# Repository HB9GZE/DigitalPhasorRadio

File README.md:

Use these SW version of the development tools:
Cube MX: 6.13.0
Cube IDE: 1.17.0
Touch GFX Generator: 4.23.0
STM32H735: 1.12.0
FreeRTOS: 1.2.0

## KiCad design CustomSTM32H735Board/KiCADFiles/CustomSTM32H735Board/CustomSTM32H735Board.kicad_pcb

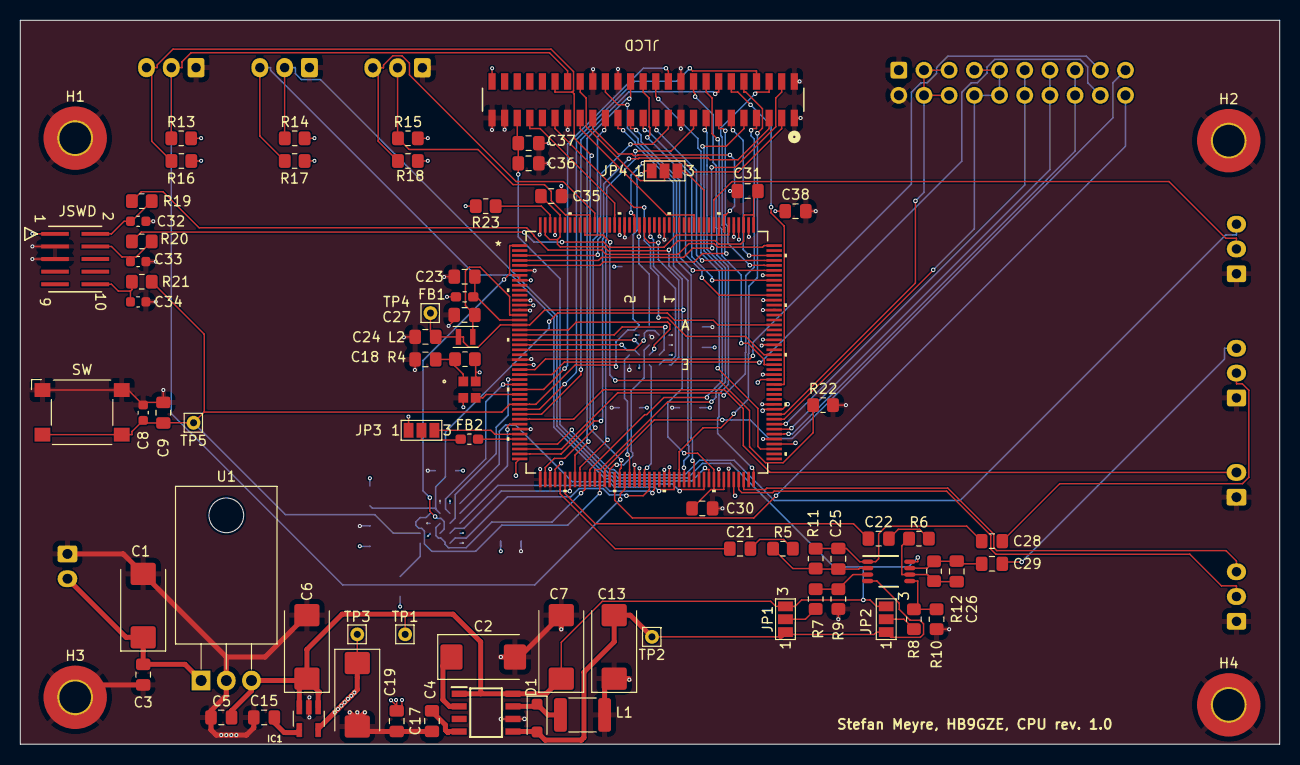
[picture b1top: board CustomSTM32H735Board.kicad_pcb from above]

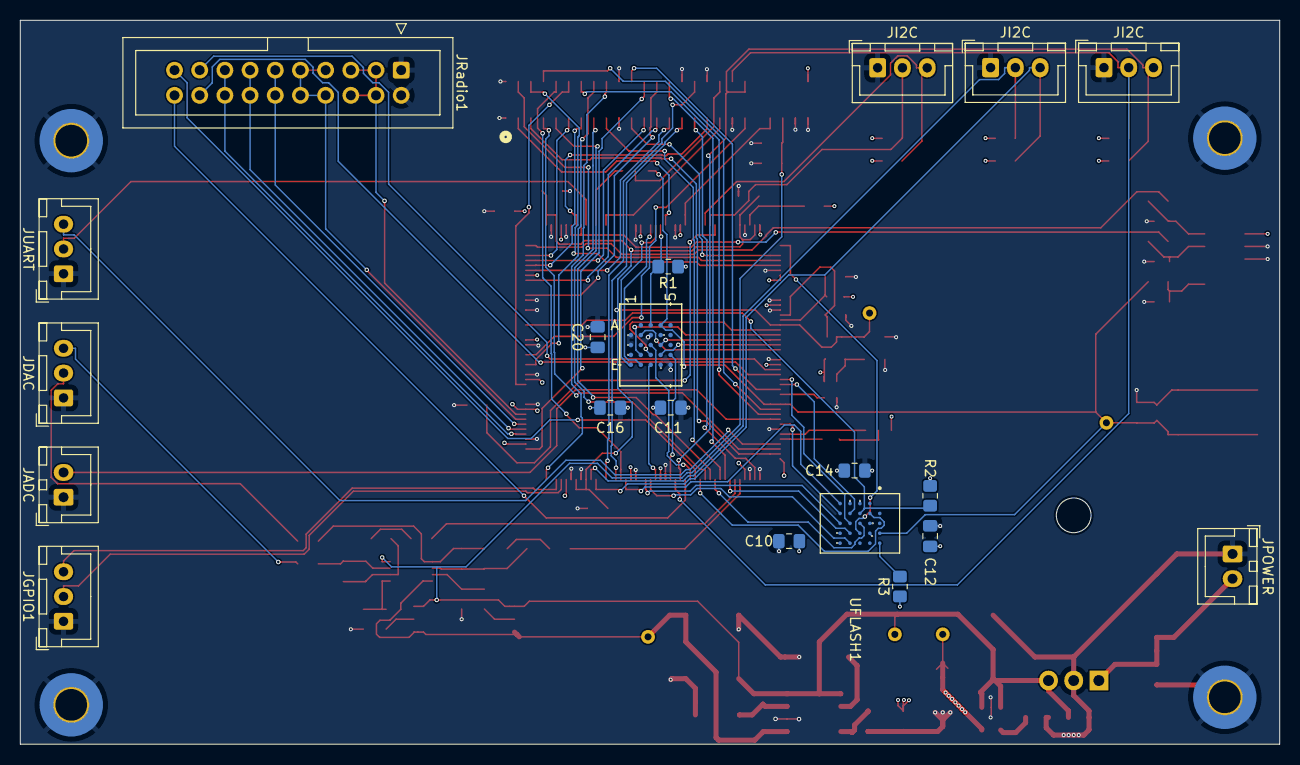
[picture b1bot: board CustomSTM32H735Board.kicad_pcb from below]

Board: 4 copper layers, 127.0 x 73.0 mm, 99 parts (20 on the bottom side), 115 nets.

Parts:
C1, C6: 47uF Tant. 25V; CP_EIA-7343-30_AVX-N_Pad2.25x2.55mm_HandSolder
C2, C19: 10uF Tant. 25V; CP_EIA-7343-30_AVX-N_Pad2.25x2.55mm_HandSolder
C3, C5, C9, C10, C11, C12, C14, C16, C17, C18, C20, C37, C38: 100nF; C_0805_2012Metric_Pad1.18x1.45mm_HandSolder
C4: optional: 82pF; C_0805_2012Metric_Pad1.18x1.45mm_HandSolder
C7: 1uF, Tant. 25V; CP_EIA-7343-30_AVX-N_Pad2.25x2.55mm_HandSolder
C8, C32, C33, C34: PGB1010603; C_0603_1608Metric
C13: 100uF Tant. 25V; CP_EIA-7343-30_AVX-N_Pad2.25x2.55mm_HandSolder
C15: 1uF; C_0805_2012Metric_Pad1.18x1.45mm_HandSolder
C21, C22, C23, C24, C28, C29, C36: 10uF; C_0805_2012Metric_Pad1.18x1.45mm_HandSolder
C25, C26: 1nF; C_0805_2012Metric_Pad1.18x1.45mm_HandSolder
C27: 220pF; C_0805_2012Metric_Pad1.18x1.45mm_HandSolder
C30, C31, C35: 4.7uF low ESR; C_0805_2012Metric_Pad1.18x1.45mm_HandSolder
D1: PMEG2010AEH; D_SOD-123F
FB1: FBMJ1608; L_0603_1608Metric_Pad1.05x0.95mm_HandSolder
FB2: FCM1608; L_0603_1608Metric_Pad1.05x0.95mm_HandSolder
H1, H2, H3, H4: MountingHole_Pad; MountingHole_3.2mm_M3_Pad_TopBottom
IC1: NCP700BSN33T1G; SOT95P275X120-5N
JADC: Conn_01x02_Socket; JST_XH_B2B-XH-A_1x02_P2.50mm_Vertical
JDAC: Conn_01x03_Socket; JST_XH_B3B-XH-A_1x03_P2.50mm_Vertical
JGPIO1: Conn_01x03_Socket; JST_XH_B3B-XH-A_1x03_P2.50mm_Vertical
JI2C, JI2C#2, JI2C#3: Conn_01x03_Socket; JST_XH_B3B-XH-A_1x03_P2.50mm_Vertical
JLCD: FLE-125-01-G-DV; CON50_2X25_UF_FLE_SAI
JP1, JP2, JP3, JP4: SolderJumper_3_Open; SolderJumper-3_P1.3mm_Open_Pad1.0x1.5mm_NumberLabels
JPOWER: Conn_01x02_Socket; JST_XH_B2B-XH-A_1x02_P2.50mm_Vertical
JRadio1: Conn_02x10_Odd_Even; IDC-Header_2x10_P2.54mm_Vertical
JSWD: FTSH-105-01-L-DV-K; CON10_2X5_DUK_FTSH_SAI-M
JUART: Conn_01x03_Socket; JST_XH_B3B-XH-A_1x03_P2.50mm_Vertical
L1: 10uH; L_1812_4532Metric_Pad1.30x3.40mm_HandSolder
L2: 2.2uH; L_Murata_DFE201610P
PS1: TPS6735ID; SOIC127P600X175-8N
R1, R2, R3, R4, R5, R6, R7, R8, R9, R10, R11, R12: 10k; R_0805_2012Metric_Pad1.20x1.40mm_HandSolder
R13, R14, R15, R16, R17, R18: 4.7k; R_0805_2012Metric_Pad1.20x1.40mm_HandSolder
R19, R20, R21: 22R; R_0805_2012Metric_Pad1.20x1.40mm_HandSolder
R22: 5k1; R_0805_2012Metric_Pad1.20x1.40mm_HandSolder
R23: 1k; R_0805_2012Metric_Pad1.20x1.40mm_HandSolder
SW: SW_Omron_B3FS; SW_SPST_Omron_B3FS-100xP
TP1, TP2, TP3, TP4, TP5: TestPoint; Pin_D0.7mm_L6.5mm_W1.8mm_FlatFork
U1: L7805; TO-220-3_Horizontal_TabDown
U2: OPA1678IDGKT; OPA1678_L
U3: STM32H735IGT6; LQFP176_STM32H735IGT6_STM-M
UFLASH1: MX25LM51245GXDI00; BGA24C100P5X5_600X800X120
UHYPERRAM1: IS66WVH16M8DBLL-100B1LI; TFBGA24_6X8_ISI
X1: NSC5004A-25M; NSC5004_NDK

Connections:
+3.3V: C10.1, C11.1, C12.1, C14.1, C16.1, C17.1, C19.1, C20.1, C38.1, FB1.1, IC1.5 (OUT), JLCD.50, JP3.1 (A), JSWD.1, R1.1, R2.1, R3.1, R4.1, R13.2, R14.2, R15.2, R16.2, R17.2, R18.2, R23.2, TP3.1, U3.7, U3.8, U3.13, U3.25, U3.44, U3.48, U3.65, U3.71, U3.84, U3.92, U3.99, U3.105, U3.113, U3.126, U3.136, U3.152, U3.160, U3.176, UFLASH1.B4 (VCC), UFLASH1.D1 (VCCQ), UFLASH1.E4 (VCCQ__1), UHYPERRAM1.B4 (VCC), UHYPERRAM1.D1 (VCCQ), UHYPERRAM1.E4 (VCCQ), X1.4 (VCC)
+5V: C5.1, C6.1, C7.1, C36.1, C37.1, IC1.1 (IN), IC1.3 (EN), JLCD.45, JP1.3 (B), JP2.3 (B), PS1.1 (EN), PS1.8 (VCC), TP1.1, U1.3 (OUT), U2.8 (V+)
-5V: C13.2, D1.2 (A), JP1.1 (A), JP2.1 (A), PS1.5 (FB), TP2.1, U2.4 (V-)
/BOOT0: R22.1, U3.167
/NRST: C8.2, C9.1, JP4.1 (A), R21.1, SW.2, TP5.1, U3.33, UFLASH1.A4 (~RESET), UHYPERRAM1.A4 (RESET#)
/PA0: JUART.3, U3.41 (PA0-UART4_TX)
/PA1: JLCD.7, U3.42 (PA1-LTDC_R2)
/PA2: JLCD.5, U3.43 (PA2-LTDC_R1)
/PA3: JLCD.31, U3.46 (PA3-LTDC_B5)
/PA4: C21.1, U3.49 (PA4-DAC1_OUT1)
/PA5: C22.1, U3.50 (PA5-DAC1_OUT2)
/PA6: U3.51 (PA6-OCTOSPIM_P1_IO3), UFLASH1.D4 (SIO3)
/PA7: JLCD.28, U3.52 (PA7-LTDC_VSYNC)
/PA8: JLCD.27, U3.127 (PA8-LTDC_B3)
/PA9: JLCD.13, U3.128 (PA9-LTDC_R5)
/PA10: JLCD.23, U3.129 (PA10-LTDC_B1)
/PA11: JLCD.11, U3.130 (PA11-LTDC_R4)
/PA13: R19.1, U3.132 (PA13(JTMS/SWDIO)-DEBUG_JTMS-SWDIO)
/PA14: R20.1, U3.138 (PA14(JTCK/SWCLK)-DEBUG_JTCK-SWCLK), U3.140
/PA15: JLCD.33, U3.139 (PA15(JTDI)-LTDC_B6)
/PB0: JLCD.9, U3.55 (PB0-LTDC_R3)
/PB1: JLCD.15, U3.56 (PB1-LTDC_R6)
/PB2: U3.57 (PB2-OCTOSPIM_P1_CLK), UFLASH1.B2 (SCLK)
/PB6: JI2C.3, R18.1, U3.165 (PB6-I2C1_SCL)
/PB7: JI2C.2, R15.1, U3.166 (PB7-I2C1_SDA)
/PB10: JI2C#3.3, R17.1, U3.78 (PB10-I2C2_SCL)
/PB11: JI2C#3.2, R14.1, U3.79 (PB11-I2C2_SDA)
/PB12: JGPIO1.2, U3.85 (PB12-GPIO_Output)
/PB13: JGPIO1.3, U3.86 (PB13-GPIO_Output)
/PB15: JLCD.18, U3.88 (PB15-LTDC_G7)
/PC0: JLCD.8, U3.34 (PC0-LTDC_G2)
/PC1: JLCD.14, U3.35 (PC1-LTDC_G5)
/PC2_C: JADC.2, U3.36 (PC2_C-ADC3_INP0)
/PC3_C: U3.37 (PC3_C-OCTOSPIM_P1_IO6), UFLASH1.E2 (SIO6)
/PC4: JLCD.17, U3.53 (PC4-LTDC_R7)
/PC5: U3.54 (PC5-OCTOSPIM_P1_DQS), UFLASH1.C3 (DQS)
/PC6: JLCD.26, U3.122 (PC6-LTDC_HSYNC)
/PC9: JLCD.25, U3.125 (PC9-LTDC_B2)
/PC11: JUART.2, U3.141 (PC11-UART4_RX)
/PD0: JP4.3 (B), U3.143
/PD2: JLCD.35, U3.145 (PD2-LTDC_B7)
/PD10: JLCD.24, U3.91 (PD10-GPIO_Output)
/PD11: JRadio1.15, JRadio1.16, U3.94 (PD11-GPIO_Output)
/PD12: JRadio1.13, JRadio1.14, U3.95 (PD12-GPIO_Output)
/PD13: JRadio1.11, JRadio1.12, U3.96 (PD13-GPIO_Output)
/PD14: JRadio1.7, JRadio1.8, JRadio1.9, JRadio1.10, U3.97 (PD14-GPIO_Output)
/PD15: JRadio1.3, JRadio1.4, JRadio1.5, JRadio1.6, U3.98 (PD15-GPIO_Output)
/PDR_ON: R23.1, U3.174
/PE2: U3.1 (PE2-OCTOSPIM_P1_IO2), UFLASH1.C4 (SIO2)
/PE4: JLCD.21, U3.3 (PE4-LTDC_B0)
/PE5: JLCD.4, U3.4 (PE5-LTDC_G0)
/PE6: JLCD.6, U3.5 (PE6-LTDC_G1)
/PE7: U3.67 (PE7-OCTOSPIM_P1_IO4), UFLASH1.D5 (SIO4)
/PE8: U3.68 (PE8-OCTOSPIM_P1_IO5), UFLASH1.E3 (SIO5)
/PE10: U3.72 (PE10-OCTOSPIM_P1_IO7), UFLASH1.E1 (SIO7)
/PE11: JLCD.10, U3.73 (PE11-LTDC_G3)
/PE12: JLCD.29, U3.74 (PE12-LTDC_B4)
/PE14: JLCD.32, U3.76 (PE14-LTDC_CLK)
/PF0: U3.18 (PF0-OCTOSPIM_P2_IO0), UHYPERRAM1.D3 (DQ0)
/PF1: U3.19 (PF1-OCTOSPIM_P2_IO1), UHYPERRAM1.D2 (DQ1)
/PF2: U3.20 (PF2-OCTOSPIM_P2_IO2), UHYPERRAM1.C4 (DQ2)
/PF3: U3.21 (PF3-OCTOSPIM_P2_IO3), UHYPERRAM1.D4 (DQ3)
/PF4: U3.22 (PF4-OCTOSPIM_P2_CLK), UHYPERRAM1.B2 (CK)
/PF6: JRadio1.17, U3.26 (PF6-TIM23_CH1)
/PF7: JRadio1.18, U3.27 (PF7-TIM23_CH2)
/PF8: U3.28 (PF8-OCTOSPIM_P1_IO0), UFLASH1.D3 (SI/SIO0)
/PF9: U3.29 (PF9-OCTOSPIM_P1_IO1), UFLASH1.D2 (SO/SIO1)
/PF10: JLCD.22, U3.30 (PF10-LTDC_DE)
/PF11: JRadio1.19, U3.58 (PF11-ADC1_INP2)
/PF12: U3.59 (PF12-OCTOSPIM_P2_DQS), UHYPERRAM1.C3 (RWDS)
/PF13: JRadio1.20, U3.60 (PF13-ADC2_INP2)
/PF14: JI2C#2.3, JLCD.40, R16.1, U3.61 (PF14-I2C4_SCL)
/PF15: JI2C#2.2, JLCD.38, R13.1, U3.62 (PF15-I2C4_SDA)
/PG0: U3.63 (PG0-OCTOSPIM_P2_IO4), UHYPERRAM1.D5 (DQ4)
/PG1: U3.66 (PG1-OCTOSPIM_P2_IO5), UHYPERRAM1.E3 (DQ5)
/PG2: JLCD.39, U3.110 (PG2-GPIO_EXTI2)
/PG6: R2.2, U3.116 (PG6-OCTOSPIM_P1_NCS), UFLASH1.C2 (~CS)
/PG10: U3.154 (PG10-OCTOSPIM_P2_IO6), UHYPERRAM1.E2 (DQ6)
/PG11: U3.155 (PG11-OCTOSPIM_P2_IO7), UHYPERRAM1.E1 (DQ7)
/PG12: R1.2, U3.156 (PG12-OCTOSPIM_P2_NCS), UHYPERRAM1.A3 (CS#)
/PG13: JLCD.3, U3.157 (PG13-LTDC_R0)
/PG15: JLCD.43, U3.161 (PG15-GPIO_Output)
/PH0: U3.31 (PH0-OSC_IN-RCC_OSC_IN), X1.3 (OUTPUT)
/PJ11: JLCD.12, U3.104 (PJ11-LTDC_G4)
/PK1: JLCD.16, U3.108 (PK1-LTDC_G6)
/VDDSMPS: C23.1, FB1.2, U3.16
/VDD_SDC: C24.1, C30.2, C31.1, C35.2, L2.1, TP4.1, U3.17, U3.80, U3.82, U3.133, U3.135, U3.172, U3.175
/VLXSMPS: C27.2, L2.2, U3.15
GND: C1.2, C2.2, C3.2, C4.2, C5.2, C6.2, C7.2, C8.1, C9.2, C10.2, C11.2, C12.2, C13.1, C14.2, C15.1, C16.2, C17.2, C18.1, C19.2, C20.2, C23.2, C24.2, C27.1, C30.1, C31.2, C32.2, C33.1, C34.1, C35.1, C36.2, C37.2, C38.2, H1.1, H2.1, H3.1, H4.1, IC1.2 (GND), JADC.1, JDAC.1, JGPIO1.1, JI2C.1, JI2C#2.1, JI2C#3.1, JLCD.1, JLCD.2, JLCD.19, JLCD.20, JLCD.30, JLCD.34, JLCD.37, JLCD.47, JLCD.49, JPOWER.1, JRadio1.1, JRadio1.2, JSWD.3, JSWD.5, JUART.1, L1.2, PS1.6 (GND), R9.1, R10.1, R22.2, SW.1, U1.2 (GND), U3.6, U3.12, U3.14, U3.24, U3.38, U3.45, U3.47, U3.64, U3.70, U3.81, U3.83, U3.93, U3.100, U3.106, U3.112, U3.119, U3.121, U3.134, U3.137, U3.151, U3.159, U3.173, UFLASH1.B3 (GND), UFLASH1.C1 (VSSQ), UFLASH1.E5 (VSSQ__1), UHYPERRAM1.B1 (CK#), UHYPERRAM1.B3 (VSS), UHYPERRAM1.C1 (VSSQ), UHYPERRAM1.E5 (VSSQ), X1.2 (GND)
unnamed: C21.2, R5.2
unnamed: C22.2, R6.2
unnamed: C32.1, JSWD.2, R19.2
unnamed: C33.2, JSWD.4, R20.2
unnamed: C34.2, JSWD.10, R21.2
unnamed: D1.1 (K), L1.1, PS1.7 (OUT)
unnamed: FB2.2, U3.40
unnamed: C15.2, IC1.4 (BYP)
unnamed: C28.2, JDAC.2
unnamed: C29.2, JDAC.3
unnamed: JP1.2 (C), R7.2
unnamed: JP2.2 (C), R8.2
unnamed: JP3.3 (B), U3.39
unnamed: FB2.1, JP3.2 (C)
unnamed: JLCD.36, JP4.2 (C)
unnamed: C1.1, C3.1, JPOWER.2, U1.1 (IN)
unnamed: C4.1, PS1.4 (COMP)
unnamed: C2.1, PS1.2 (REF)
unnamed: R7.1, R9.2, U2.3 (IN+)
unnamed: C25.1, R5.1, R11.2, U2.2 (IN-)
unnamed: C25.2, C28.1, R11.1, U2.1 (OUT)
unnamed: R8.1, R10.2, U2.5 (IN+)
unnamed: C26.1, R6.1, R12.2, U2.6 (IN-)
unnamed: C26.2, C29.1, R12.1, U2.7 (OUT)
unnamed: R3.2, UFLASH1.A5 (~ECS)
unnamed: C18.2, R4.2, X1.1 (STAND-BY)

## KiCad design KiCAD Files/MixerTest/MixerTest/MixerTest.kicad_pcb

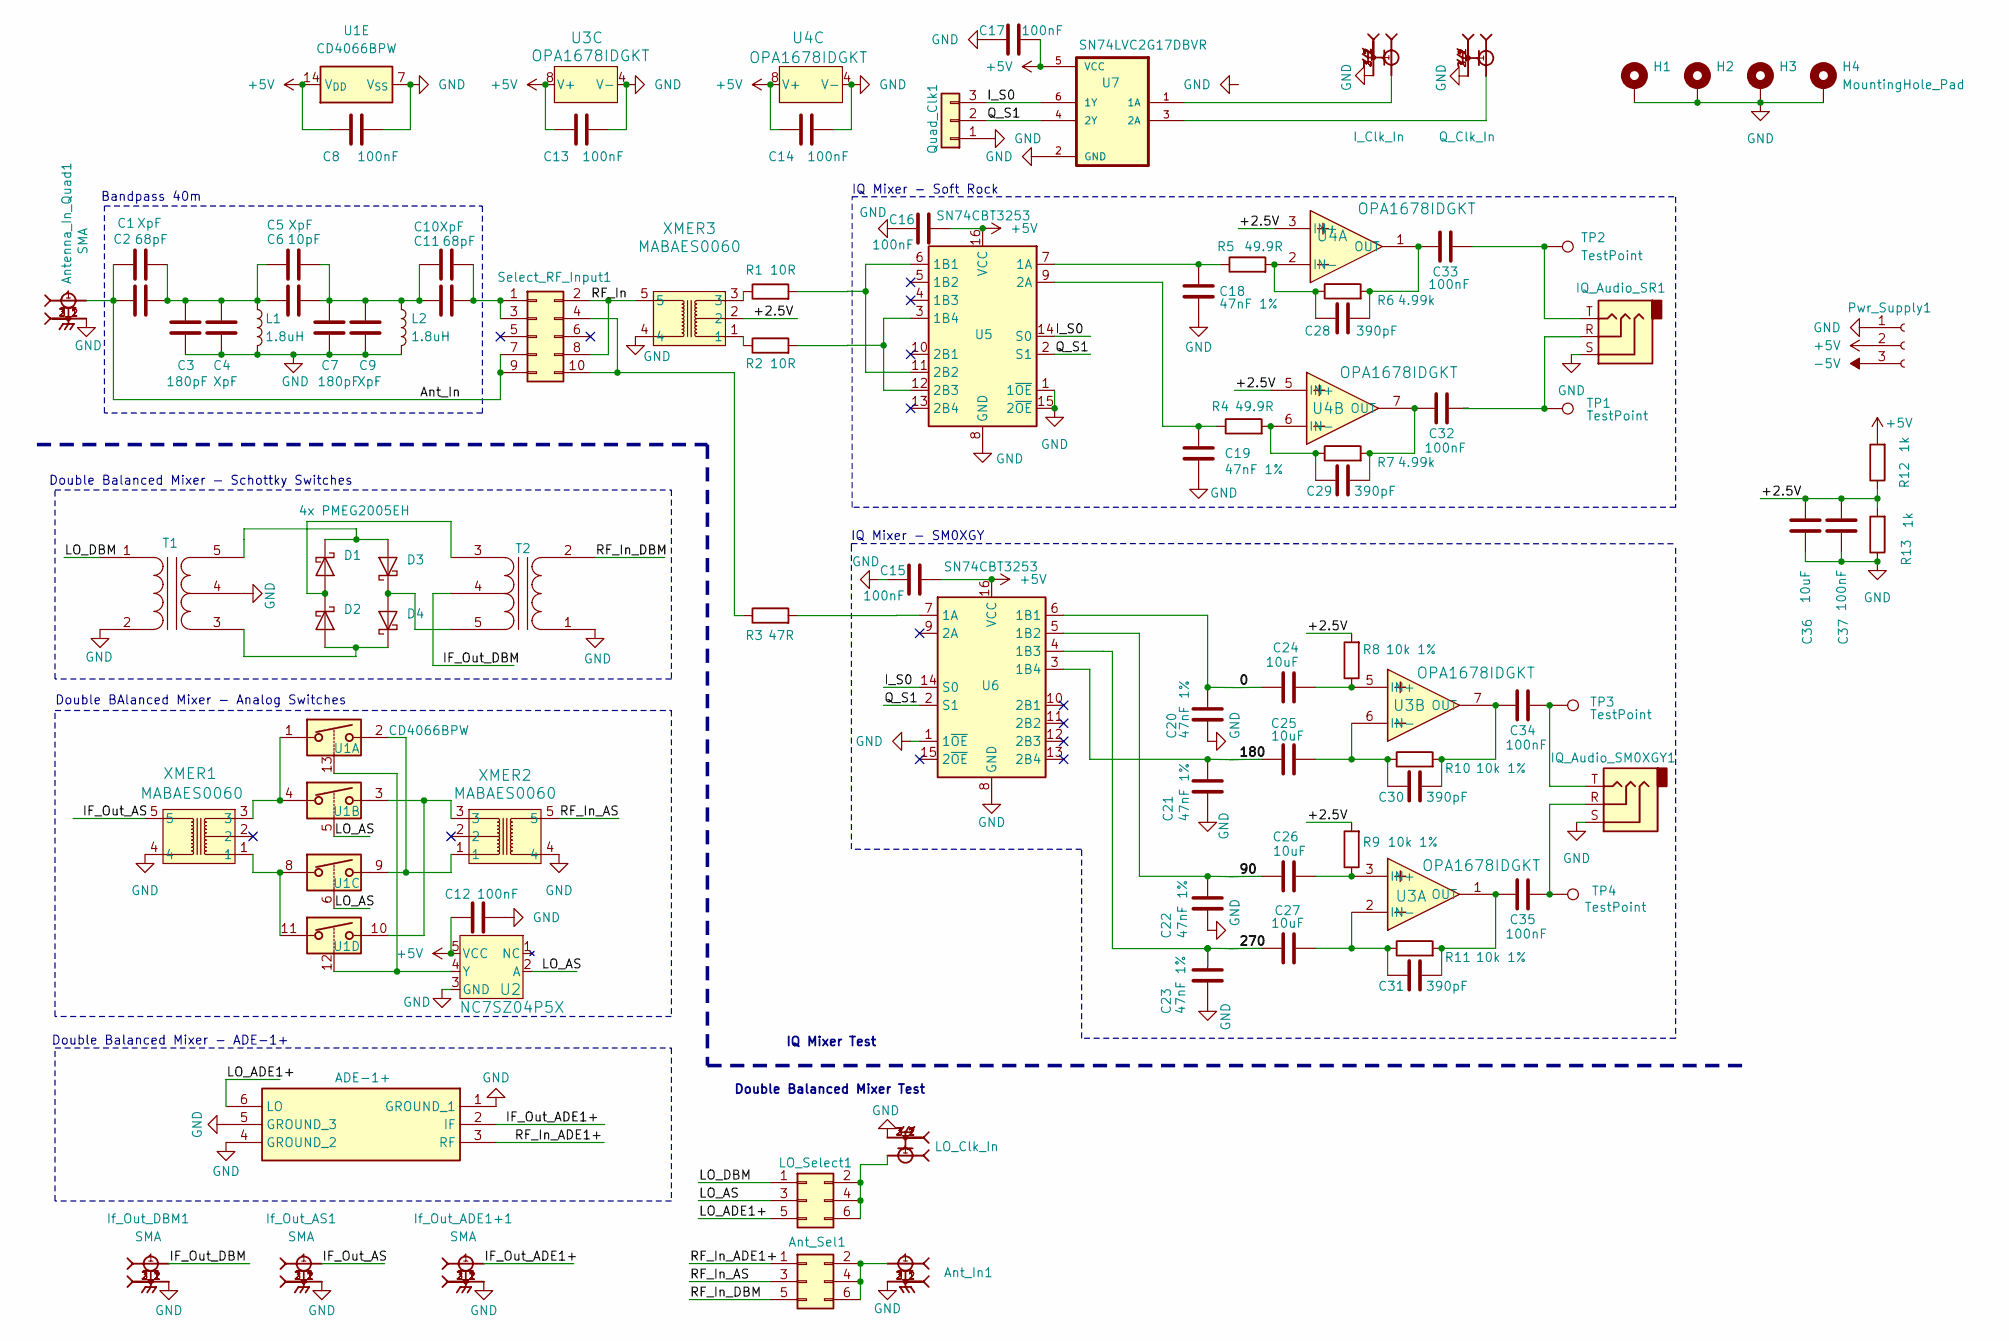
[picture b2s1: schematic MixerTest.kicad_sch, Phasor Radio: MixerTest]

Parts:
Ant_In1: SMA; SAMTEC_SMA-J-P-H-ST-EM1
Ant_Sel1: Conn_02x03_Odd_Even; PinHeader_2x03_P2.54mm_Vertical
Antenna_In_Quad1: SMA; SAMTEC_SMA-J-P-H-ST-EM1
C1, C4, C5, C9, C10: XpF; C_0805_2012Metric_Pad1.18x1.45mm_HandSolder
C2, C11: 68pF; C_0805_2012Metric_Pad1.18x1.45mm_HandSolder
C3, C7: 180pF; C_0805_2012Metric_Pad1.18x1.45mm_HandSolder
C6: 10pF; C_0805_2012Metric_Pad1.18x1.45mm_HandSolder
C8, C12, C13, C14, C15, C16, C17, C32, C33, C34, C35, C37: 100nF; C_0805_2012Metric_Pad1.18x1.45mm_HandSolder
C18, C19, C20, C21, C22, C23: 47nF 1%; C_0805_2012Metric_Pad1.18x1.45mm_HandSolder
C24, C25, C26, C27, C36: 10uF; C_0805_2012Metric_Pad1.18x1.45mm_HandSolder
C28, C29, C30, C31: 390pF; C_0805_2012Metric_Pad1.18x1.45mm_HandSolder
D1: 4x PMEG2005EH; D_SOD-123F
D2, D3, D4: PMEG2005EH; D_SOD-123F
H1, H2, H3, H4: MountingHole_Pad; MountingHole_2.5mm_Pad_TopBottom
IC1: ADE-1+; ADE1Mix; Manufacturer_Part_Number ADE-1+; Mouser Part Number 139-ADE-1
IQ_Audio_SM0XGY1: AudioJack3; Jack_3.5mm_CUI_SJ-3523-SMT_Horizontal
IQ_Audio_SR1: AudioJack3; Jack_3.5mm_CUI_SJ-3523-SMT_Horizontal
I_Clk_In: SMA; SAMTEC_SMA-J-P-H-ST-EM1
If_Out_ADE1+1: SMA; SAMTEC_SMA-J-P-H-ST-EM1
If_Out_AS1: SMA; SAMTEC_SMA-J-P-H-ST-EM1
If_Out_DBM1: SMA; SAMTEC_SMA-J-P-H-ST-EM1
L1, L2: 1.8uH; L_Toroid_Vertical_L19.1mm_W8.1mm_P7.10mm_Bourns_5700
LO_Clk_In: SMA; SAMTEC_SMA-J-P-H-ST-EM1
LO_Select1: Conn_02x03_Odd_Even; PinSocket_2x03_P2.54mm_Vertical
Pwr_Supply1: Conn_01x03_Socket; JST_EH_B3B-EH-A_1x03_P2.50mm_Vertical
Q_Clk_In: SMA; SAMTEC_SMA-J-P-H-ST-EM1
Quad_Clk1: Conn_01x03; PinHeader_1x03_P2.54mm_Vertical
R1, R2: 10R; R_0805_2012Metric_Pad1.20x1.40mm_HandSolder
R3: 47R; R_0805_2012Metric_Pad1.20x1.40mm_HandSolder
R4, R5: 49.9R; R_0805_2012Metric_Pad1.20x1.40mm_HandSolder
R6, R7: 4.99k; R_0805_2012Metric_Pad1.20x1.40mm_HandSolder
R8, R9, R10, R11: 10k 1%; R_0805_2012Metric_Pad1.20x1.40mm_HandSolder
R12, R13: 1k; R_0805_2012Metric_Pad1.20x1.40mm_HandSolder
Select_RF_Input1: Conn_02x05_Odd_Even; PinHeader_2x05_P2.54mm_Vertical
T1, T2: Transformer_1P_SS_SNM
TP1, TP2, TP3, TP4: TestPoint; TestPoint_Loop_D1.80mm_Drill1.0mm_Beaded
U1: CD4066BPW; TSSOP-14_4.4x5mm_P0.65mm
U2: NC7SZ04P5X; SC-88A-5_1P35X2P2_ONS
U3, U4: OPA1678IDGKT; OPA1678_L
U5, U6: SN74CBT3253; SOP65P640X110-16N
U7: SN74LVC2G17DBVR; SOT95P280X145-6N
XMER1, XMER2, XMER3: MABAES0060; MABAES0060_MCM

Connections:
+5V: C8.1, C12.2, C13.1, C14.1, C15.2, C16.2, C17.2, Pwr_Supply1.2, R12.2, U1.14 (V_{DD}), U2.5 (VCC), U3.8 (V+), U4.8 (V+), U5.16 (VCC), U6.16 (VCC), U7.5 (VCC)
-5V: Pwr_Supply1.3
/0: C20.1, C24.1, U6.6 (1B1)
/90: C22.1, C26.1, U6.5 (1B2)
/180: C21.1, C25.1, U6.3 (1B4)
/270: C23.1, C27.1, U6.4 (1B3)
/Ant_In: Antenna_In_Quad1.1, C1.1, C2.1, Select_RF_Input1.7, Select_RF_Input1.9
/IF_Out_ADE1+: IC1.2 (IF), If_Out_ADE1+1.1
/IF_Out_AS: If_Out_AS1.1, XMER1.5
/IF_Out_DBM: If_Out_DBM1.1, T2.4 (SC)
/I_S0: Quad_Clk1.3, U5.14 (S0), U6.14 (S0), U7.6 (1Y)
/LO_ADE1+: IC1.6 (LO), LO_Select1.5
/LO_AS: LO_Select1.3, U1.5, U1.6, U2.2 (A)
/LO_DBM: LO_Select1.1, T1.1 (AA)
/Q_S1: Quad_Clk1.2, U5.2 (S1), U6.2 (S1), U7.4 (2Y)
/RF_In: Select_RF_Input1.2, Select_RF_Input1.8, XMER3.5
/RF_In_ADE1+: Ant_Sel1.1, IC1.3 (RF)
/RF_In_AS: Ant_Sel1.3, XMER2.5
/RF_In_DBM: Ant_Sel1.5, T2.2 (AB)
unnamed: Ant_In1.1, Ant_Sel1.2, Ant_Sel1.4, Ant_Sel1.6
unnamed: C1.2, C2.2, C3.2, C4.2, C5.1, C6.2, L1.1
unnamed: C5.2, C6.1, C7.2, C9.1, C10.1, C11.1, L2.1
unnamed: C32.2, IQ_Audio_SR1.R, TP1.1
unnamed: C33.2, IQ_Audio_SR1.T, TP2.1
unnamed: C34.2, IQ_Audio_SM0XGY1.T, TP3.1
unnamed: C35.2, IQ_Audio_SM0XGY1.R, TP4.1
unnamed: D1.2 (A), D2.1 (K), T2.3 (SA)
unnamed: D1.1 (K), D3.2 (A), T1.5 (SB)
unnamed: D2.2 (A), D4.1 (K), T1.3 (SA)
unnamed: D3.1 (K), D4.2 (A), T2.5 (SB)
unnamed 30: LO_Clk_In.1, LO_Select1.2, LO_Select1.4, LO_Select1.6; also elsewhere on the board
unnamed 31: I_Clk_In.1, U7.1 (1A); also elsewhere on the board
unnamed 32: Q_Clk_In.1, U7.3 (2A); also elsewhere on the board
unnamed: R1.1, XMER3.3
unnamed: R2.1, XMER3.1
unnamed: C10.2, C11.2, Select_RF_Input1.1, Select_RF_Input1.3
unnamed: R3.1, Select_RF_Input1.4, Select_RF_Input1.10
unnamed: U1.1, U1.4, XMER1.3
unnamed: U1.2, U1.9, XMER2.1
unnamed: U1.3, U1.10, XMER2.3
unnamed: U1.8, U1.11, XMER1.1
unnamed: U1.12, U1.13, U2.4 (Y)
unnamed: C26.2, R9.1, U3.3 (IN+)
unnamed: C27.2, C31.1, R11.1, U3.2 (IN-)
unnamed: C31.2, C35.1, R11.2, U3.1 (OUT)
unnamed: C24.2, R8.1, U3.5 (IN+)
unnamed: C25.2, C30.1, R10.1, U3.6 (IN-)
unnamed: C30.2, C34.1, R10.2, U3.7 (OUT)
unnamed: C28.1, R5.2, R6.1, U4.2 (IN-)
unnamed: C29.1, R4.2, R7.1, U4.6 (IN-)
unnamed: C29.2, C32.1, R7.2, U4.7 (OUT)
unnamed: C18.1, R5.1, U5.7 (1A)
unnamed: R1.2, U5.6 (1B1), U5.11 (2B2)
unnamed: R2.2, U5.3 (1B4), U5.12 (2B3)
unnamed: C19.1, R4.1, U5.9 (2A)
unnamed: R3.2, U6.7 (1A)

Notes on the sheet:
IQ Mixer - Soft Rock
Bandpass 40m
Double Balanced Mixer - ADE-1+
Double Balanced Mixer Test
IQ Mixer Test
Double BAlanced Mixer - Analog Switches
Double Balanced Mixer - Schottky Switches
IQ Mixer - SM0XGY

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
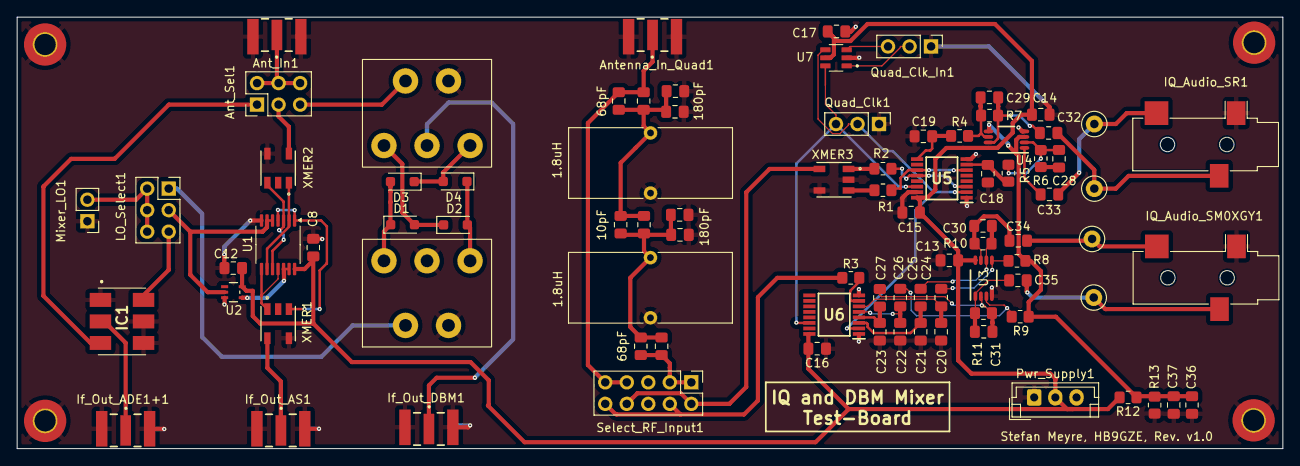
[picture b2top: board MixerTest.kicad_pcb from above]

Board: 2 copper layers, 149.4 x 50.9 mm, 91 parts (0 on the bottom side), 59 nets.

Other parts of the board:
Mixer_LO1: Conn_01x02_Socket; PinHeader_1x02_P2.54mm_Vertical
Quad_Clk_In1: Conn_01x03; PinHeader_1x03_P2.54mm_Vertical

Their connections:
unnamed 30: Mixer_LO1.2; also elsewhere on the board
unnamed 31: Quad_Clk_In1.2; also elsewhere on the board
unnamed 32: Quad_Clk_In1.3; also elsewhere on the board

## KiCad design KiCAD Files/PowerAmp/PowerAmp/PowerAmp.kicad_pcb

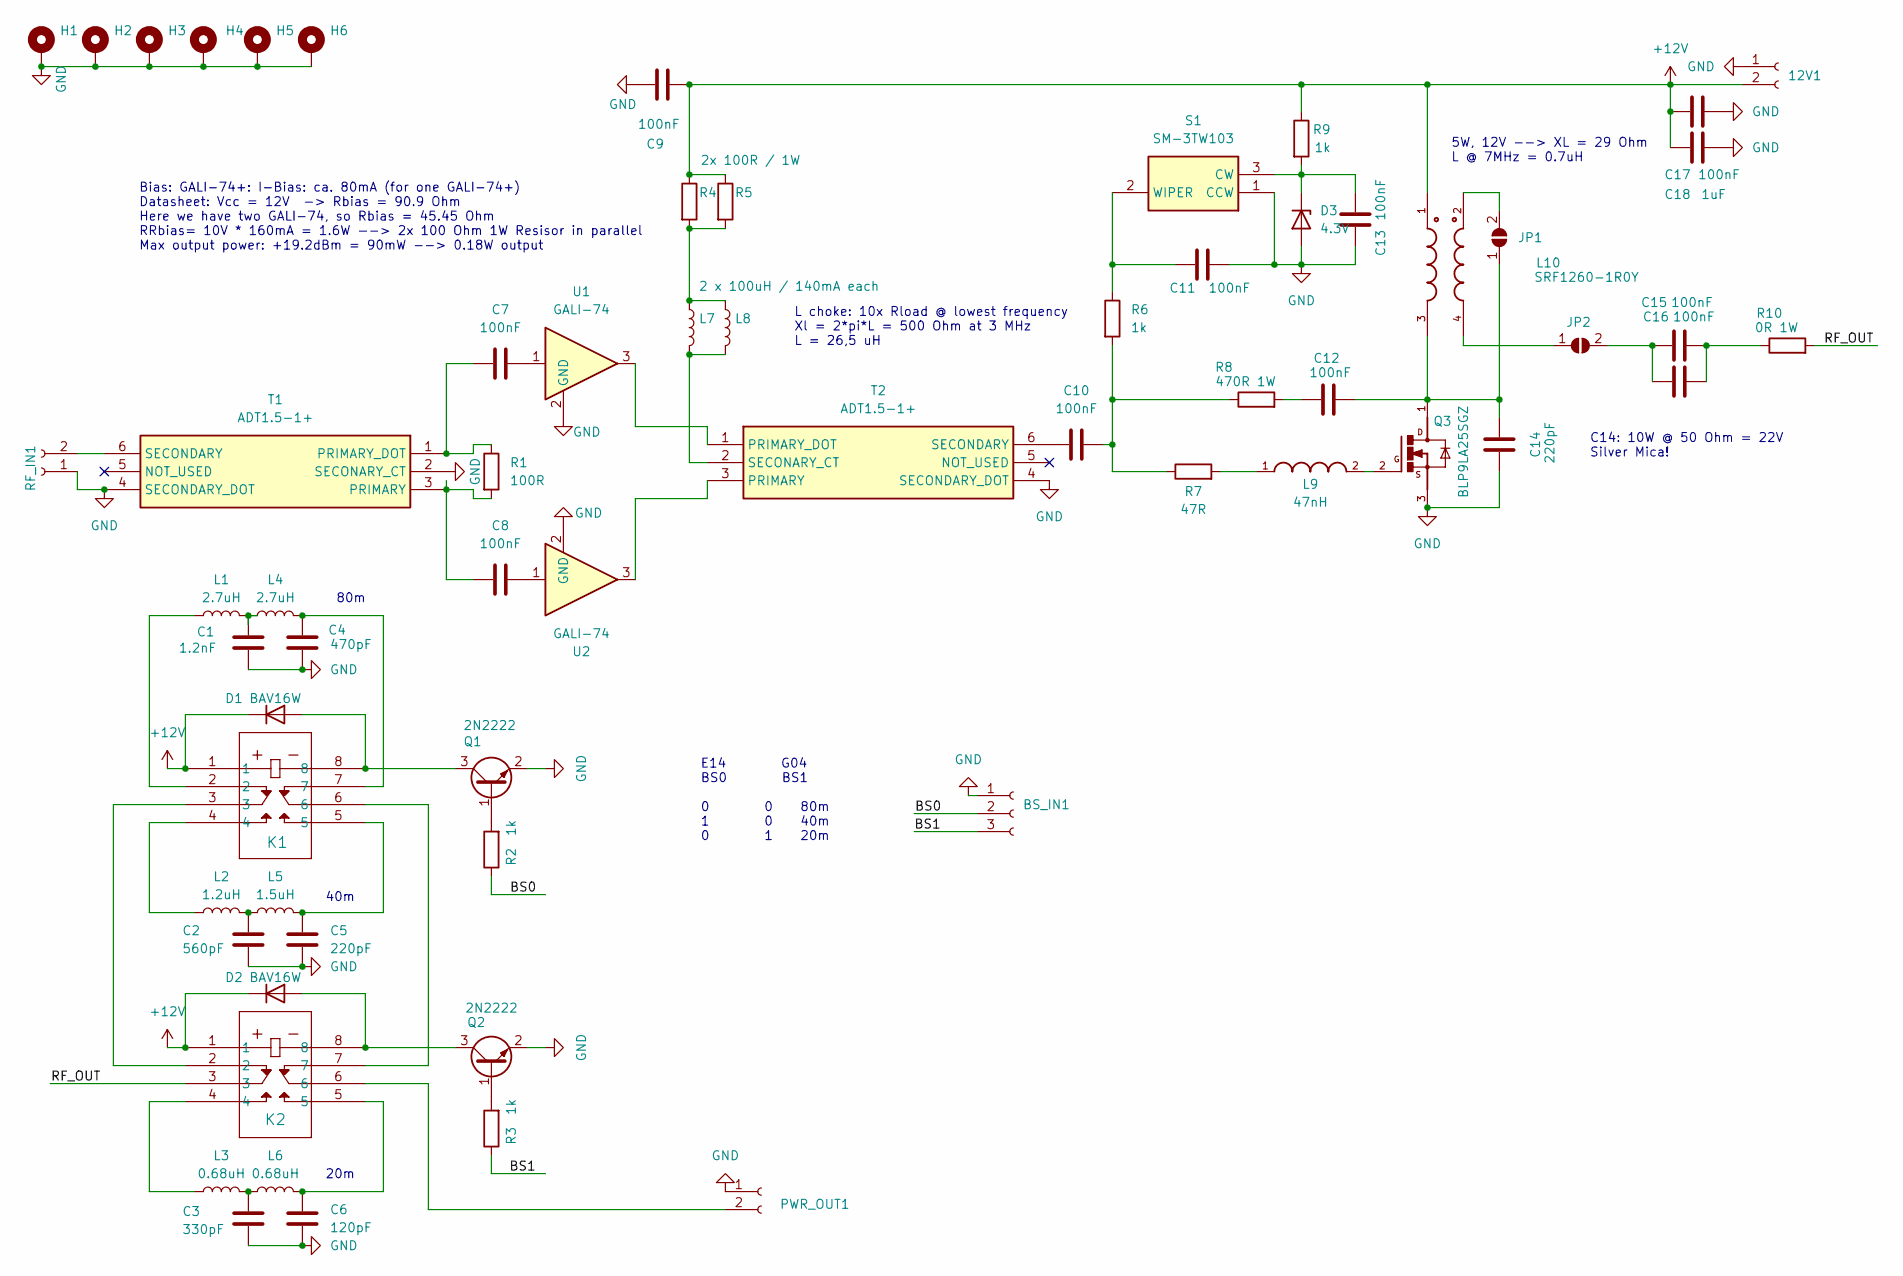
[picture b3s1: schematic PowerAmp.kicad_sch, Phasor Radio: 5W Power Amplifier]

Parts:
12V1: Conn_01x02_Socket; PinHeader_1x02_P1.00mm_Vertical_SMD
BS_IN1: Conn_01x03_Socket; PinHeader_1x03_P1.00mm_Vertical_SMD
C1: 1.2nF; C_0805_2012Metric_Pad1.18x1.45mm_HandSolder
C2: 560pF; C_0805_2012Metric_Pad1.18x1.45mm_HandSolder
C3: 330pF; C_0805_2012Metric_Pad1.18x1.45mm_HandSolder
C4: 470pF; C_0805_2012Metric_Pad1.18x1.45mm_HandSolder
C5: 220pF; C_0805_2012Metric_Pad1.18x1.45mm_HandSolder
C6: 120pF; C_0805_2012Metric_Pad1.18x1.45mm_HandSolder
C7, C8, C9, C10, C11, C12, C13, C15, C16, C17: 100nF; C_0805_2012Metric_Pad1.18x1.45mm_HandSolder
C14: 220pF; C_2220_5750Metric_Pad1.97x5.40mm_HandSolder
C18: 1uF; C_0805_2012Metric_Pad1.18x1.45mm_HandSolder
D1, D2: BAV16W; D_SOD-123
D3: 4.3V; D_SOD-123
H1, H2, H3, H4, H5, H6: MountingHole_Pad; MountingHole_2.7mm_M2.5_DIN965_Pad_TopBottom
JP1, JP2: SolderJumper_2_Open; SolderJumper-2_P1.3mm_Open_Pad1.0x1.5mm
K1, K2: G6K-2F-Y DC3; G6K-2F-Y DC3_OMR
L1, L4: 2.7uH; L_Toroid_Vertical_L16.3mm_W7.1mm_P7.11mm_SMD
L2: 1.2uH; L_Toroid_Vertical_L16.3mm_W7.1mm_P7.11mm_SMD
L3, L6: 0.68uH; L_Toroid_Vertical_L16.3mm_W7.1mm_P7.11mm_SMD
L5: 1.5uH; L_Toroid_Vertical_L16.3mm_W7.1mm_P7.11mm_SMD
L7: 2 x 100uH / 140mA each; L_0805_2012Metric_Pad1.15x1.40mm_HandSolder
L8: 30uH / 200mA; L_0805_2012Metric_Pad1.15x1.40mm_HandSolder
L9: 47nH; INDC2624X203N
L10: SRF1260-1R0Y; IND_SRF1260-1R0Y; DigiKey_Part_Number SRF1260-1R0YTR-ND
PWR_OUT1: Conn_01x02_Socket; PinHeader_1x02_P1.00mm_Vertical_SMD
Q1, Q2: 2N2222; SOT-23
Q3: BLP9LA25SGZ; BLP9LA25SGZ_SOT1483-1_TO270
R1: 100R; R_0805_2012Metric_Pad1.20x1.40mm_HandSolder
R2, R3, R6, R9: 1k; R_0805_2012Metric_Pad1.20x1.40mm_HandSolder
R4: 2x 100R / 1W; R_2512_6332Metric_Pad1.40x3.35mm_HandSolder
R5: 100R 1W; R_2512_6332Metric_Pad1.40x3.35mm_HandSolder
R7: 47R; R_0805_2012Metric_Pad1.20x1.40mm_HandSolder
R8: 470R 1W; R_2512_6332Metric_Pad1.40x3.35mm_HandSolder
R10: 0R 1W; R_2512_6332Metric_Pad1.40x3.35mm_HandSolder
RF_IN1: Conn_01x02_Socket; PinHeader_1x02_P1.00mm_Vertical_SMD
S1: SM-3TW103; SM3TW103; Manufacturer_Part_Number SM-3TW103; Mouser Part Number 229-SM-3TW103
T1, T2: ADT1.5-1+; ADT151; Manufacturer_Part_Number ADT1.5-1+; Mouser Part Number 139-ADT1.5-1
U1, U2: GALI-74; SOT-89-3

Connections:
+12V: 12V1.2, C9.1, C17.2, C18.2, D1.1 (K), D2.1 (K), K1.1, K2.1, L10.1, R4.1, R5.1, R9.1; also elsewhere on the board
/BS0: BS_IN1.2, R2.1; also elsewhere on the board
/BS1: BS_IN1.3, R3.1; also elsewhere on the board
/RF_OUT: K2.3, R10.2
GND: 12V1.1, BS_IN1.1, C1.2, C2.2, C3.2, C4.2, C5.2, C6.2, C9.2, C11.2, C13.1, C14.1, C17.1, C18.1, D3.2 (A), H1.1, H2.1, H3.1, H4.1, H5.1, H6.1, PWR_OUT1.1, Q1.2 (E), Q2.2 (E), Q3.3, RF_IN1.1, S1.1 (CCW), T1.2 (SECONARY_CT), T1.4 (SECONDARY_DOT), T2.4 (SECONDARY_DOT), U1.2 (GND), U2.2 (GND); also elsewhere on the board
unnamed: C1.1, L1.2, L4.1
unnamed: C2.1, L2.2, L5.1
unnamed: C3.1, L3.2, L6.1
unnamed: C4.1, K1.7, L4.2
unnamed: C5.1, K1.5, L5.2
unnamed: C6.1, K2.5, L6.2
unnamed: C7.2, U1.1
unnamed: C8.2, U2.1
unnamed: C10.2, R6.2, R7.1, R8.1
unnamed: C12.1, R8.2
unnamed: C15.2, C16.2, R10.1
unnamed: D1.2 (A), K1.8, Q1.3 (C)
unnamed: D2.2 (A), K2.8, Q2.3 (C)
unnamed: C13.2, D3.1 (K), R9.2, S1.3 (CW)
unnamed: C12.2, C14.2, JP1.1 (A), L10.3, Q3.1
unnamed: JP1.2 (B), L10.2
unnamed: JP2.1 (A), L10.4
unnamed: C15.1, C16.1, JP2.2 (B)
unnamed: K1.2, L1.1
unnamed: K1.3, K2.2
unnamed: K1.4, L2.1
unnamed: K1.6, K2.7
unnamed: K2.4, L3.1
unnamed: L7.1, L8.1, R4.2, R5.2
unnamed: L9.1, R7.2
unnamed: L9.2, Q3.2
unnamed 31: K2.6, PWR_OUT1.2; also elsewhere on the board
unnamed: Q1.1 (B), R2.2
unnamed: Q2.1 (B), R3.2
unnamed 34: RF_IN1.2, T1.6 (SECONDARY); also elsewhere on the board
unnamed: C11.1, R6.1, S1.2 (WIPER)
unnamed: C8.1, R1.2, T1.3 (PRIMARY)
unnamed: C7.1, R1.1, T1.1 (PRIMARY_DOT)
unnamed: T2.3 (PRIMARY), U2.3
unnamed: T2.1 (PRIMARY_DOT), U1.3
unnamed: L7.2, L8.2, T2.2 (SECONARY_CT)
unnamed: C10.1, T2.6 (SECONDARY)

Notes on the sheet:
40m
20m
L choke: 10x Rload @ lowest frequency Xl = 2*pi*L = 500 Ohm at 3 MHz L = 26,5 uH
80m
5W, 12V --> XL = 29 Ohm L @ 7MHz = 0.7uH
Bias: GALI-74+: I-Bias: ca. 80mA (for one GALI-74+) Datasheet: Vcc = 12V -> Rbias = 90.9 Ohm Here we have two GALI-74, so Rbias = 45.45 Ohm RRbias= 10V * 160mA = 1.6W --> 2x 100 Ohm 1W Resisor in parallel Max output power: +19.2dBm = 90mW --> 0.18W output
E14 G04 BS0 BS1 0 0 80m 1 0 40m 0 1 20m
C14: 10W @ 50 Ohm = 22V Silver Mica!

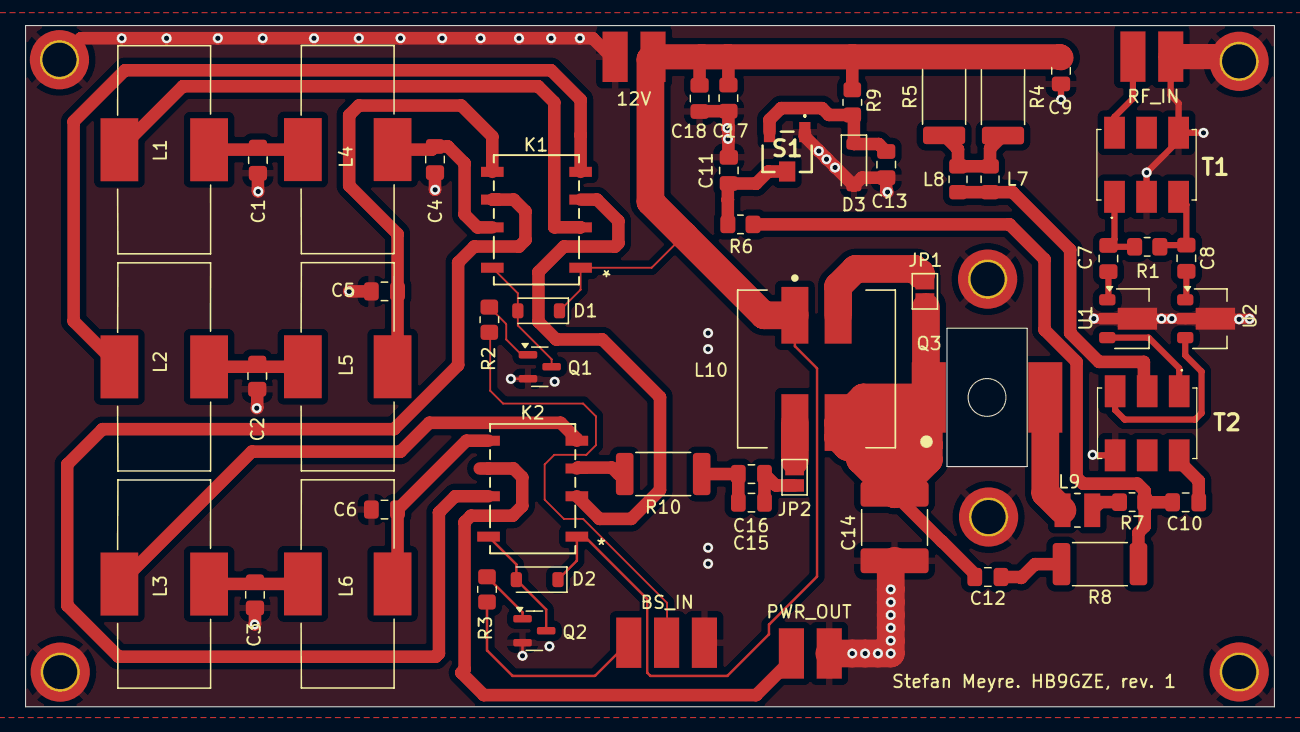
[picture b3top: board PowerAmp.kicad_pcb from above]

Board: 2 copper layers, 99.0 x 54.0 mm, 63 parts (0 on the bottom side), 42 nets.

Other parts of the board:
12V: Conn_01x02_Socket; PinHeader_1x02_P1.00mm_Vertical_SMD
BS_IN: Conn_01x03_Socket; PinHeader_1x03_P1.00mm_Vertical_SMD
PWR_OUT: Conn_01x02_Socket; PinHeader_1x02_P1.00mm_Vertical_SMD
RF_IN: Conn_01x02_Socket; PinHeader_1x02_P1.00mm_Vertical_SMD

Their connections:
+12V: 12V.2; also elsewhere on the board
/BS0: BS_IN.2; also elsewhere on the board
/BS1: BS_IN.3; also elsewhere on the board
GND: 12V.1, BS_IN.1, PWR_OUT.1, RF_IN.1; also elsewhere on the board
unnamed 31: PWR_OUT.2; also elsewhere on the board
unnamed 34: RF_IN.2; also elsewhere on the board
